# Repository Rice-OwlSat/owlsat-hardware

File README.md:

# owlsat-hardware
Hardware repo - based on OakwoodEngineering's Obi Wan Komputer

# Tools needed
KiCAD - FOSS EDA software from https://www.kicad.org/download/ 

LTSPICE - Circuit simulator for Windows and MacOS, works well under Wine with Linux (https://www.analog.com/en/resources/design-tools-and-calculators/ltspice-simulator.html)

(or alternatively use Falstad (https://www.falstad.com/circuit/) as it's a simpler interface and just as good for simple circuits that don't require specialized ICs)

git - FOSS version control software. Use Git Bash for Windows and optionally GitHub Desktop or another GUI for easier management.

# To-do (this is somewhat still a jumble of useful ideas)

- ~~Copy OWK repo hardware~~
- figure out what parts to keep and what to shave off
- consolidate everything we need into one board
- use ADM1176 properly or remove (per mlyle's suggestion)
- make transimpedance amp EUV measurement subsystem
- add magnetorquer subsystem (max22200 full bridge driver)
- improve solar charging subsystem if needed (test existing boards first!)
- make MRAM work with RP2350 (important, but requires bootloader and possibly sdk modification (and I don't yet know how to do this))
- change connectors to be less expensive but still reliable (however we will likely still have to use something expensive for the important connectors like battery)
- reorganize power domains
- re-layout board
- ensure we can build circuitpython firmware for our specific board

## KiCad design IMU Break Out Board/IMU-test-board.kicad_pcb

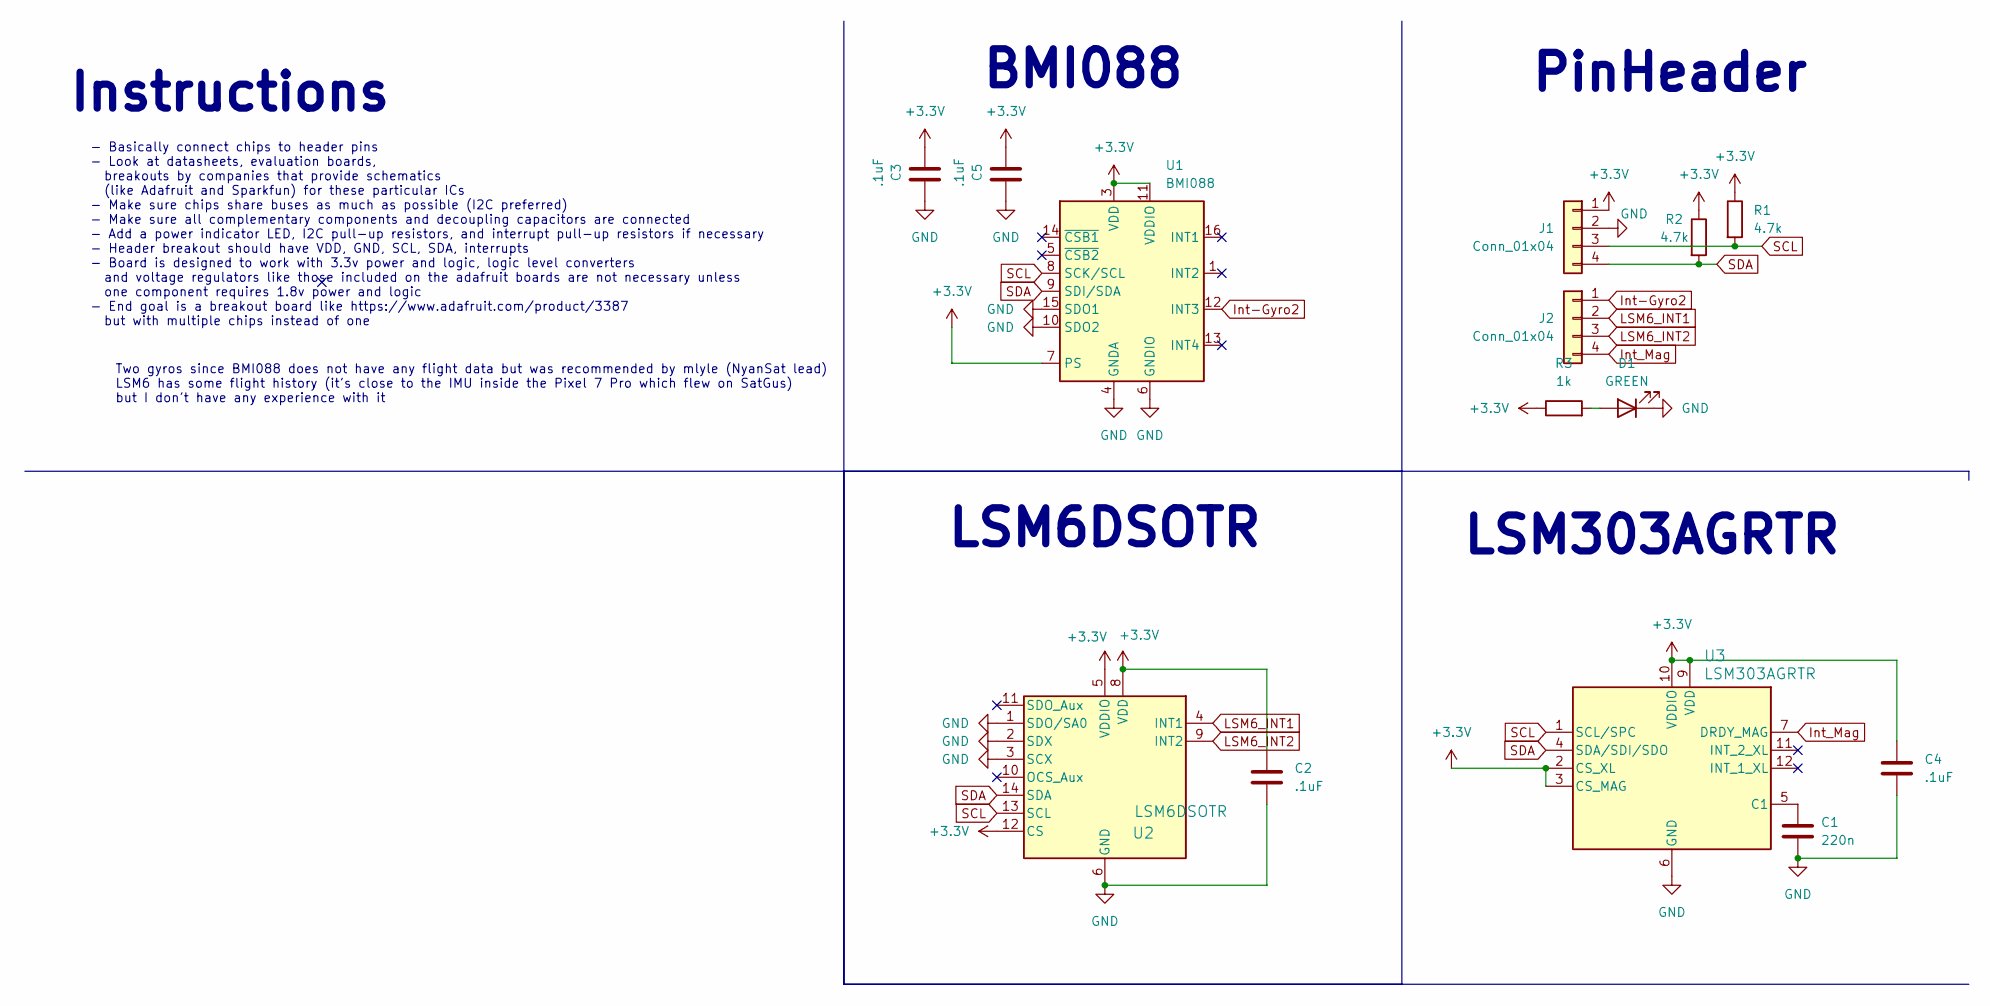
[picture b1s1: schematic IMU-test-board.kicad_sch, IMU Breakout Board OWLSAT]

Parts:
C1: 220n; C_0603_1608Metric
C2, C3, C4, C5: .1uF; C_0603_1608Metric
D1: GREEN; LED_0603_1608Metric
J1, J2: Conn_01x04; PinHeader_1x04_P2.54mm_Vertical
R1, R2: 4.7k; R_0603_1608Metric
R3: 1k; R_0603_1608Metric
U1: BMI088; Bosch_LGA-16_4.5x3mm_P0.5mm_LayoutBorder7x1y_ClockwisePinNu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
U2: LSM6DSOTR; LGA14L
U3: LSM303AGRTR; PQFN50P200X200X100-12N

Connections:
+3.3V: C2.1, C3.1, C4.1, C5.1, J1.1, R1.1, R2.1, R3.1, U1.3 (VDD), U1.7 (PS), U1.11 (VDDIO), U2.5 (VDDIO), U2.8 (VDD), U2.12 (CS), U3.2 (CS_XL), U3.3 (CS_MAG), U3.9 (VDD), U3.10 (VDDIO)
GND: C1.2, C2.2, C3.2, C4.2, C5.2, D1.1 (K), J1.2, U1.2 (GNDA), U1.4 (GNDA), U1.6 (GNDIO), U1.10 (SDO2), U1.15 (SDO1), U2.1 (SDO/SA0), U2.2 (SDX), U2.3 (SCX), U2.6 (GND), U2.7 (GND), U3.6 (GND), U3.8 (GND)
Int-Gyro2: J2.1, U1.12 (INT3)
Int_Mag: J2.4, U3.7 (DRDY_MAG)
LSM6_INT1: J2.2, U2.4 (INT1)
LSM6_INT2: J2.3, U2.9 (INT2)
unnamed: D1.2 (A), R3.2
unnamed: C1.1, U3.5 (C1)
SCL: J1.3, R1.2, U1.8 (SCK/SCL), U2.13 (SCL), U3.1 (SCL/SPC)
SDA: J1.4, R2.2, U1.9 (SDI/SDA), U2.14 (SDA), U3.4 (SDA/SDI/SDO)

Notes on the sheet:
BMI088
LSM303AGRTR
PinHeader
LSM6DSOTR
- Basically connect chips to header pins - Look at datasheets, evaluation boards, breakouts by companies that provide schematics (like Adafruit and Sparkfun) for these particular ICs - Make sure chips share buses as much as possible (I2C preferred) - Make sure all complementary components and decou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
Instructions
Two gyros since BMI088 does not have any flight data but was recommended by mlyle (NyanSat lead) LSM6 has some flight history (it's close to the IMU inside the Pixel 7 Pro which flew on SatGus) but I don't have any experience with it

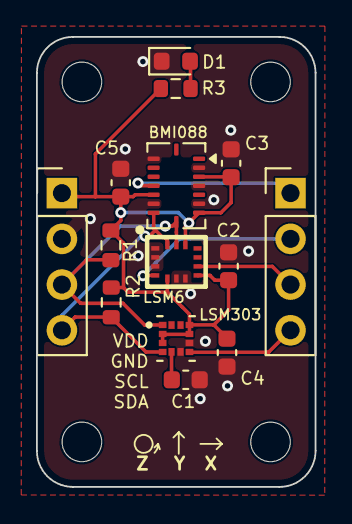
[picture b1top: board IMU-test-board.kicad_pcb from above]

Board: 2 copper layers, 15.5 x 25.0 mm, 14 parts (0 on the bottom side), 10 nets.

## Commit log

2025-07-17 Add KiCAD files
2025-07-24 Minor update to readme
    added circuitpython compat reminder
2025-10-20 Add RP2350 (and onboarding I guess)
2025-12-18 RP2350 Scheme
    Added RP2350B schematic to Avionics sub schematic. Added hierarchy schematics for each of the sub schematics for the RP2350B and completed schematics for 4/6. The other 2 need objects to be added to 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
2025-12-24 Downloaded the Footprints for RP2350B
    Downloaded the ABM8-272-T3 for the crystal and the SM03B-SRSS-TB for the JST connector, though the later is not correct (I think) because it lacks mechanical pads within the footprint.
2025-12-29 Consolidate/mostly finalize avionics
    Add RP2350 components to same sheet as RP2350, replace flash with MRAM
2026-06-13 edits
2026-06-19 Added footprints
    Added the schematics + footprints for current forerunners of GPS antenna and receiver
2026-06-22 Fixed poorly uploaded symbols
    Fixed poorly uploaded symbols but also added some components in the GPS+CAN subsheet.
2026-06-22 Add radiation findings summary for OwlSat project
    Added a comprehensive summary written by Opus 4.8 of radiation findings and references for the OwlSat project, including direct answers to radiation-related questions, supporting details, and mitigat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
2026-06-27 Clean up IMU board and make it breadboard compatible
